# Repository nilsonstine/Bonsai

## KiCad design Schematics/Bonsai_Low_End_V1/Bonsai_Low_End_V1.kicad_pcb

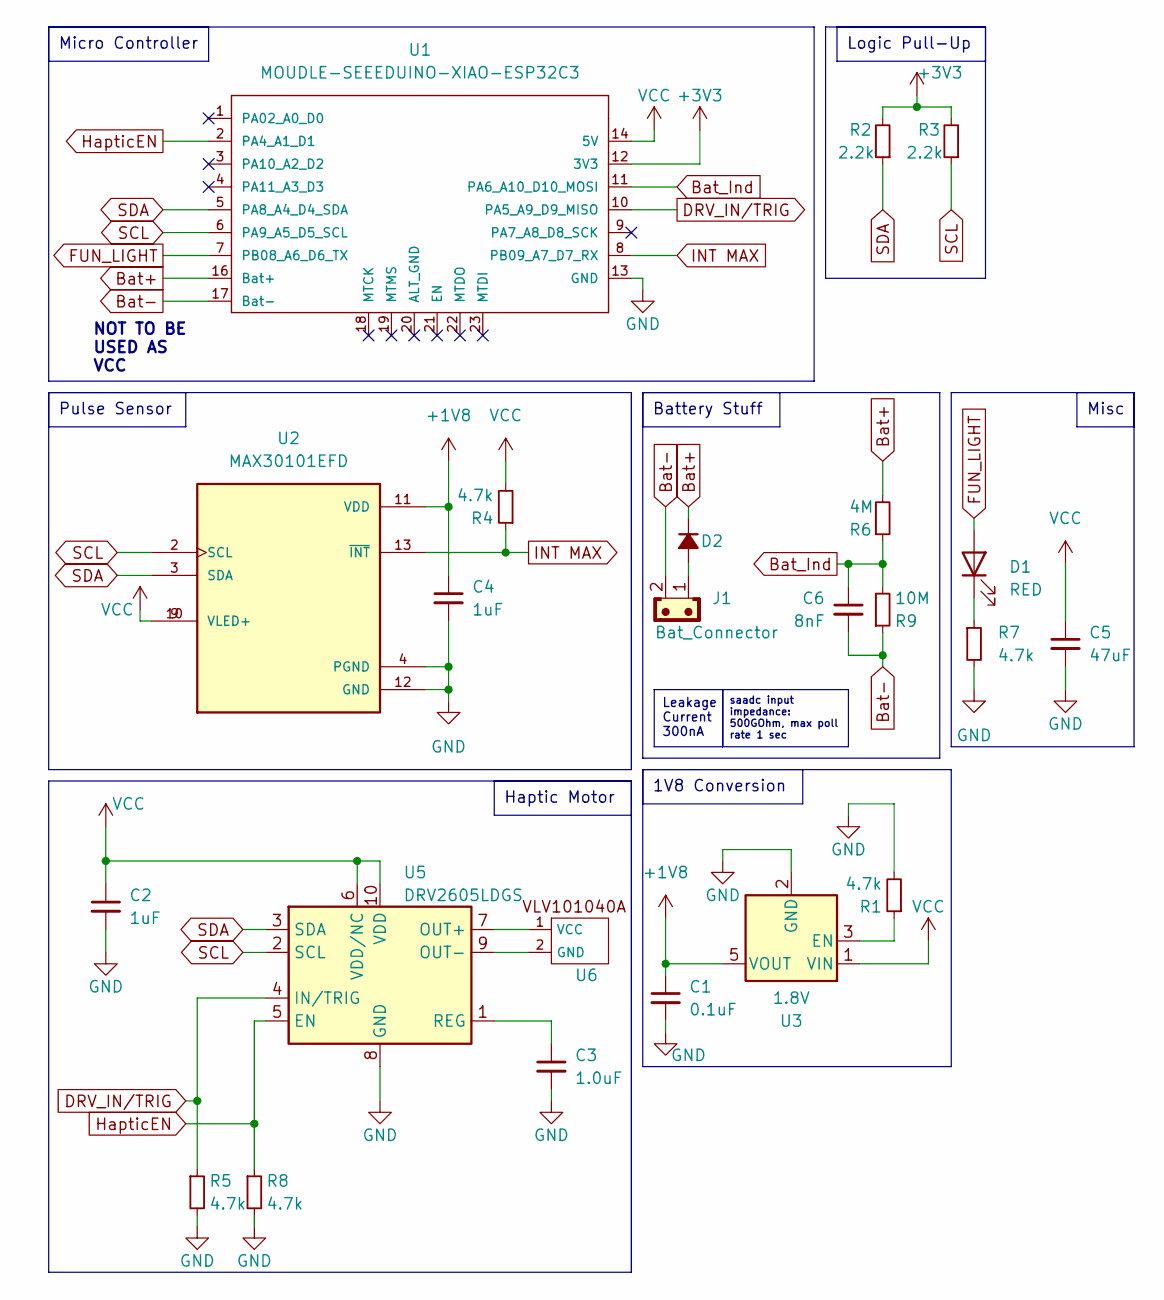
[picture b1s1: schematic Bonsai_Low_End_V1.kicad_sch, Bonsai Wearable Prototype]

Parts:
C1: 0.1uF; C_0603_1608Metric_Pad1.08x0.95mm_HandSolder
C2, C4: 1uF; C_0805_2012Metric_Pad1.18x1.45mm_HandSolder
C3: 1.0uF; C_0603_1608Metric_Pad1.08x0.95mm_HandSolder
C5: 47uF; C_0805_2012Metric_Pad1.18x1.45mm_HandSolder
C6: 8nF; C_0805_2012Metric_Pad1.18x1.45mm_HandSolder
D1: RED; LED_0603_1608Metric_Pad1.05x0.95mm_HandSolder
D2: D_Small_Filled; D_0603_1608Metric_Pad1.05x0.95mm_HandSolder
J1: Bat_Connector; JST_SH_SM02B-SRSS-TB_1x02-1MP_P1.00mm_Horizontal
R1, R4, R5, R7, R8: 4.7k; R_0603_1608Metric_Pad0.98x0.95mm_HandSolder
R2, R3: 2.2k; R_0603_1608Metric_Pad0.98x0.95mm_HandSolder
R6: 4M; R_0603_1608Metric_Pad0.98x0.95mm_HandSolder
R9: 10M; R_0603_1608Metric_Pad0.98x0.95mm_HandSolder
U1: MOUDLE-SEEEDUINO-XIAO-ESP32C3; xiap esp32c3_PCB_ ADDED BATTERY PADS
U2: MAX30101EFD; PSON80P560X330X165-14N; PARTREV 2
U3: 1.8V; SOT-23-5
U5: DRV2605LDGS; VSSOP-10_3x3mm_P0.5mm
U6: VLV101040A

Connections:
+1V8: C1.1, C4.1, U2.11 (VDD), U3.5 (VOUT)
+3V3: R2.2, R3.2, U1.12 (3V3)
Bat+: D2.1 (K), R6.2, U1.16 (Bat+)
Bat-: C6.2, J1.2, R9.1, U1.17 (Bat-)
Bat_Ind: C6.1, R6.1, R9.2, U1.11 (PA6_A10_D10_MOSI)
DRV_IN/TRIG: R5.1, U1.10 (PA5_A9_D9_MISO), U5.4 (IN/TRIG)
FUN_LIGHT: D1.2 (A), U1.7 (PB08_A6_D6_TX)
GND: C1.2, C2.2, C3.2, C4.2, C5.2, R1.2, R5.2, R7.2, R8.2, U1.13 (GND), U2.4 (PGND), U2.12 (GND), U3.2 (GND), U5.8 (GND)
HapticEN: R8.1, U1.2 (PA4_A1_D1), U5.5 (EN)
INT MAX: R4.1, U1.8 (PB09_A7_D7_RX), U2.13 (~INT)
unnamed: D1.1 (K), R7.1
unnamed: D2.2 (A), J1.1
unnamed: R1.1, U3.3 (EN)
unnamed: U5.7 (OUT+), U6.1 (VCC)
unnamed: U5.9 (OUT-), U6.2 (GND)
unnamed: C3.1, U5.1 (REG)
SCL: R3.1, U1.6 (PA9_A5_D5_SCL), U2.2 (SCL), U5.2 (SCL)
SDA: R2.1, U1.5 (PA8_A4_D4_SDA), U2.3 (SDA), U5.3 (SDA)
VCC: C2.1, C5.1, R4.2, U1.14 (5V), U2.9 (VLED+), U2.10 (VLED+), U3.1 (VIN), U5.6 (VDD/NC), U5.10 (VDD)

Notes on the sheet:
NOT TO BE USED AS VCC
Pulse Sensor
Leakage Current 300nA
saadc input impedance: 500GOhm, max poll rate 1 sec
Haptic Motor
Logic Pull-Up
Misc
Micro Controller
Battery Stuff
1V8 Conversion

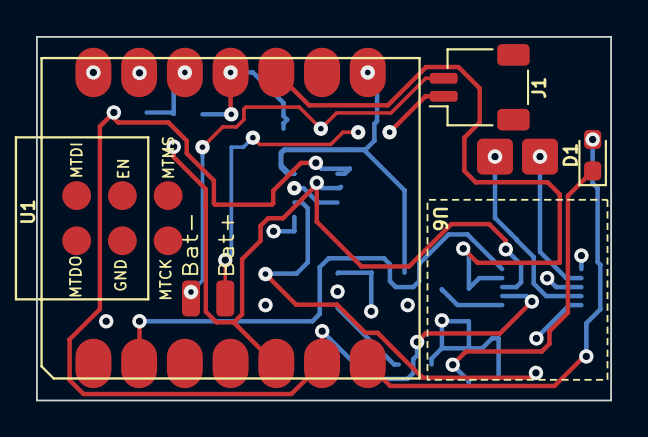
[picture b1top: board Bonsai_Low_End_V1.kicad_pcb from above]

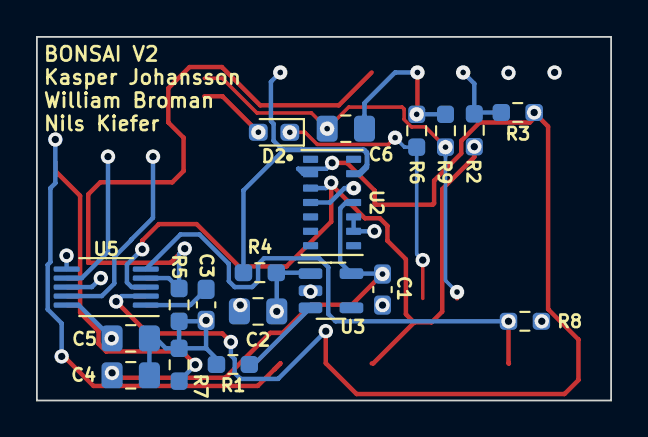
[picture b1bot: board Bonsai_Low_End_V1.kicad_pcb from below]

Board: 4 copper layers, 31.9 x 20.2 mm, 23 parts (19 on the bottom side), 19 nets.

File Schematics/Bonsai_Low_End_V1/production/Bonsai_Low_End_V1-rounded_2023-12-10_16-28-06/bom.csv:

Designator,Footprint,Quantity,Value,LCSC Part #
"C1, C7",0603,2,1uF,
C2,0805,1,1uF,
C3,0603,1,1.0uF,
"C4, C5, C8, C9",0805,4,4.7uF,
C6,0805,1,8nF,
D1,0603,1,RED,
D2,0603,1,D_Small_Filled,
J1,JST_SH_SM02B-SRSS-TB_1x02-1MP_P1.00mm_Horizontal,1,Bat_Connector,
"R1, R2, R3, R4, R5, R7, R8",0603,7,4.7k,
R6,0603,1,4M,
R9,0603,1,10M,
U1,xiap esp32c3_PCB_ ADDED BATTERY PADS,1,MOUDLE-SEEEDUINO-XIAO-ESP32C3,
U2,PSON80P560X330X165-14N,1,MAX30101EFD,
U3,SOT-23-5,1,1.8V,
U5,VSSOP-10_3x3mm_P0.5mm,1,DRV2605LDGS,
U6,VLV101040A,1,~,

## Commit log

2023-08-14 initial
2023-08-16 somewhat working, but not quite there yet
2023-08-16 new lib with patches
2023-08-17 added heartsensor code
2023-08-17 backup
2023-08-17 all seems to be working
2023-08-28 added seeed esp32
2023-08-28 Redundant comments
2023-10-22 Added Schematics and Reorganized
2023-10-22 Starting Schematics
2023-10-22 Before Everything Breaks
2023-10-22 Added Driver and Haptic Motor
2023-10-23 last psuh before feedback
2023-10-23 Made PCB
2023-10-23 addition
2023-10-26 prior feedback fix
2023-10-26 Improved
2023-10-26 fixed orientation of nmos
2023-10-26 prior disaster
2023-10-26 prior symbol change
2023-10-26 finished pcb
2023-10-26 various pcb fixes
2023-11-03 fixed save issue
2023-11-04 Converted PCB to 4 layer
2023-11-04 Updated to standard values
2023-11-10 Added SilkScreen References
2023-11-10 Fixing Useless Files
2023-11-10 pls work
2023-11-10 Updated pdf
2023-11-19 added name
2023-12-10 prior rounding tracks
2023-12-10 rounded tracks
2023-12-10 sent to jlcpcb
